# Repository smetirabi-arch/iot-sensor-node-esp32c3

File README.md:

# iot-sensor-node-esp32c3
Custom open-source ESP32-C3-02 IoT sensor node PCB featuring integrated TP4056 Li-ion battery charging with protection, BME280 environmental sensing, ambient light/sound sensors, I2C OLED display, and microSD/flash storage. Includes full KiCad hardware design, ESP32 firmware, and documentation. MIT licensed. Ideal for IoT prototyping.

SmartNode — ESP32-C3 IoT Sensor Node with Integrated Li-ion Power Management

Custom open-source ESP32-C3-02 IoT sensor node PCB featuring integrated TP4056 Li-ion battery charging with protection, BME280 environmental sensing, ambient light/sound sensors, I2C OLED display, and microSD/flash storage. Includes full KiCad hardware design, ESP32 firmware, and documentation. MIT licensed. Ideal for IoT prototyping.

Table of Contents

Overview
Key Features
System Architecture
Hardware Details

Microcontroller
Power Management
Sensors & Storage
Display & Indicators

Design Highlights
Applications
Repository Structure
Getting Started
Documentation
License

Overview

SmartNode is a custom-designed PCB for compact, battery-powered IoT applications, built around the ESP32-C3-02 SoC. The board integrates a complete power management subsystem using the TP4056 Li-ion battery charger IC, enabling safe, efficient charging of a single-cell Li-ion battery while supporting a rich set of onboard sensors and peripherals for real-world environmental monitoring and data logging.

This repository provides everything needed to build, program, and deploy the board: schematics, PCB layout files, firmware source code, and full documentation.

Key Features

Microcontroller: ESP32-C3-02 SoC — Wi-Fi and Bluetooth Low Energy (BLE) connectivity
Power Management: TP4056 IC for single-cell Li-ion charging with thermal regulation
Battery Protection: Under-voltage lockout (UVLO) and trickle charging
Environmental Sensing: BME280 (temperature, humidity, pressure), ambient light sensor, sound sensor
Storage: MicroSD card reader + onboard flash memory
Display: I2C OLED for real-time data visualization
Power Inputs: USB-C (charging + data) and JST LiPo connector
Status Indicators: LEDs for charging and full-charge states

System Architecture

SmartNode is organized into four functional subsystems, coordinated by the ESP32-C3-02 over I2C and SPI:

Processing & Connectivity — ESP32-C3-02 SoC
Power Management — TP4056 charging circuit and voltage regulation
Sensing & Storage — Environmental sensors, OLED display, SD card, flash memory
User Feedback — Status LEDs and display output

Hardware Details

Microcontroller

The ESP32-C3-02 is a RISC-V-based SoC with integrated Wi-Fi and BLE. It was chosen for its low power consumption, sufficient I2C/SPI/UART peripheral support, native wireless stack, and small footprint — making it well suited for compact, battery-powered IoT devices.

Power Management

TP4056 charging IC — provides constant-current/constant-voltage (CC/CV) charging, thermal regulation, and programmable charge current (set via external resistor)
Automatic charge termination — prevents overcharging once the battery reaches full voltage
UVLO & trickle charging — protects against deep discharge and safely recovers depleted batteries
USB-C — powers the system and charges the battery; also used for firmware flashing/debugging
JST LiPo connector — direct single-cell Li-ion/LiPo battery connection
Regulated power delivery — ensures stable operation whether powered via USB or battery

Sensors & Storage

ComponentFunctionBME280Temperature, humidity, and barometric pressure sensingAmbient light sensorEnvironmental light-level detectionSound sensorAmbient noise/acoustic sensingMicroSD card readerLocal, expandable data storageOnboard flash memoryFast, non-removable storage for firmware/cached data

All sensors communicate over I2C (SD storage typically over SPI), keeping the architecture modular and easily expandable with additional I2C devices.

Display & Indicators

I2C OLED display — real-time visualization of live sensor readings, no external device required
LED indicators — signal charging status (charging vs. fully charged)

Design Highlights

Integrated Power Supply — USB-C and TP4056 work together to manage charging and system power seamlessly
Modular, Expandable Architecture — additional I2C sensors can be added with minimal hardware changes
Safe, Efficient Charging — programmable current and automatic termination protect battery health
Compact, Reliable PCB Layout — optimized traces to minimize power loss, with thermal management around the TP4056 and other heat-sensitive components

Applications

IoT edge devices for environmental monitoring
Battery-powered data logging systems
General-purpose prototyping platform for ESP32-based hardware projects

Repository Structure

├── hardware/         # KiCad schematic and PCB layout files
├── firmware/          # ESP32-C3-02 source code
├── docs/
│   ├── datasheets/    # Component datasheets (TP4056, sensors, etc.)
│   ├── assembly.md    # Step-by-step assembly instructions
│   └── testing.md     # Testing and validation procedures
├── LICENSE
└── README.md

Documentation

Detailed documentation is available in the docs/ folder, including:

Component datasheets
Assembly instructions
Testing and validation procedures

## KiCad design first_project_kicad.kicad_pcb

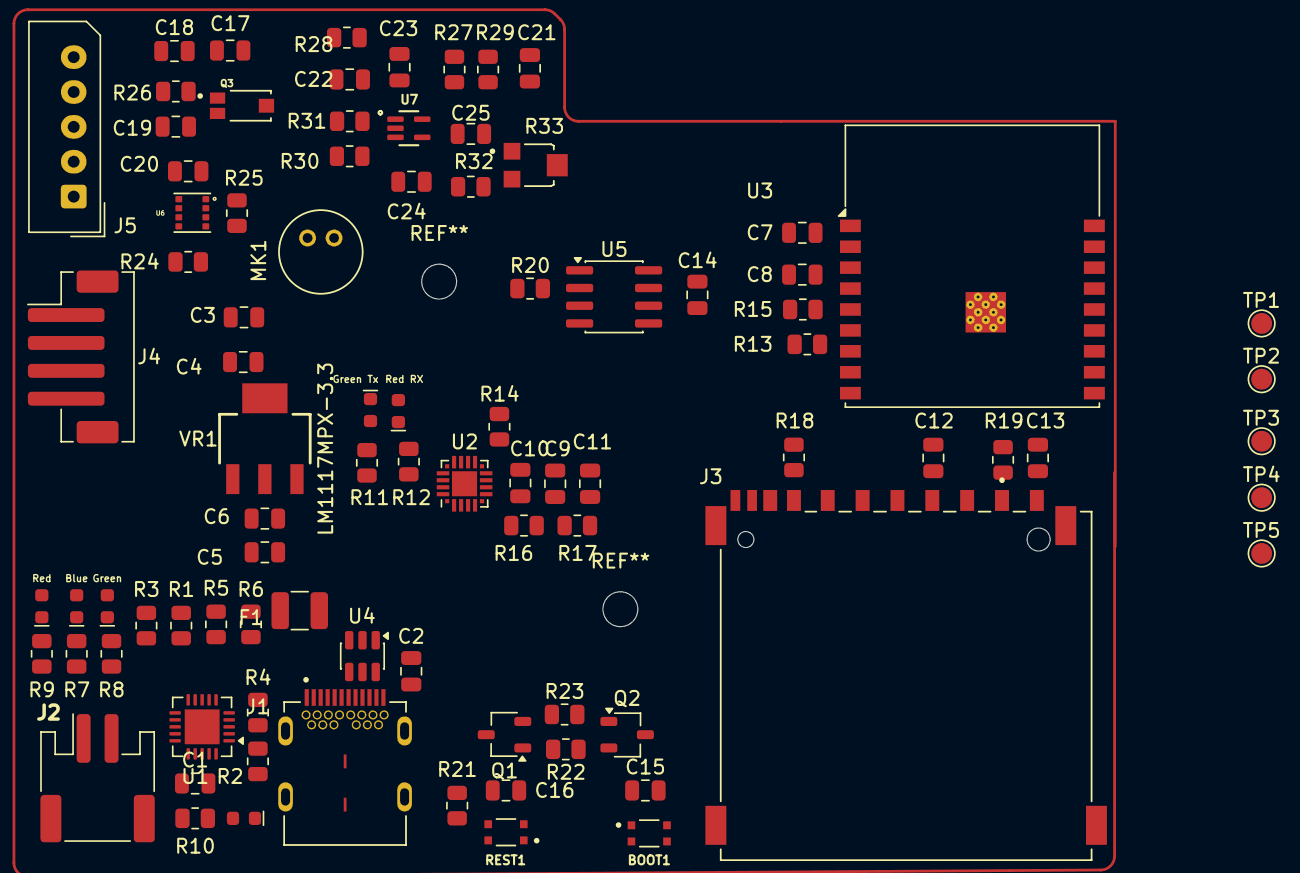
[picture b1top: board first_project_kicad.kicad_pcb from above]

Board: 4 copper layers, 89 parts (0 on the bottom side), 54 nets, no tracks yet.

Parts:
BOOT1: USLPT2819DT2TR; SW_USLPT2819DT2TR
C1, C11, C16: 1u; C_0805_2012Metric
C2, C7, C9, C13, C14, C15, C17, C20, C21, C23: 0.1u; C_0805_2012Metric
C3, C5, C6, C8, C12, C24: 10u; C_0805_2012Metric
C4: C; C_0805_2012Metric
C10: 4.7U; C_0805_2012Metric
C18, C19, C22: 10n; C_0805_2012Metric
C25: 100P; C_0805_2012Metric
D1: Blue; LED_0603_1608Metric
D2: Green; LED_0603_1608Metric
D3, D4: Red; LED_0603_1608Metric
D5: Green Tx; LED_0603_1608Metric
D6: Red RX; LED_0603_1608Metric
F1: 0ZCH0110AF2E; Fuse_1210_3225Metric
J1: SS-52400-002; BELFUSE_SS-52400-002
J2: B2B-PH-SM4-TB; JST_PH_S2B-PH-SM4-TB_1x02-1MP_P2.00mm_Horizontal
J3: GSD090012SEU; AMPHENOL_GSD090012SEU
J4: B4B-XH-AM_(LF)(SN); JST_PH_B4B-PH-SM4-TB_1x04-1MP_P2.00mm_Vertical
J5: 535170530; Molex_SPOX_5267-05A_1x05_P2.50mm_Vertical
MK1: CMC-5042PF-AC; CUI_CMC-5042PF-AC
Q1, Q2: BC817-40; TSOT-23
Q3: TEMT6000X01; TRANS_TEMT6000X01
R1: 2k; R_0805_2012Metric
R2, R4: 5k; R_0805_2012Metric
R3: 20k; R_0805_2012Metric
R5, R6, R13, R15, R18, R19, R20, R21, R22, R23, R26: 10k; R_0805_2012Metric
R7, R8, R9: 470; R_0805_2012Metric
R10, R11, R12: 330; R_0805_2012Metric
R14, R30: 1K; R_0805_2012Metric
R16: 47K5; R_0805_2012Metric
R17: 22K1; R_0805_2012Metric
R24, R25: 4K7; R_0805_2012Metric
R27, R29: 2K; R_0805_2012Metric
R28, R31: 1M; R_0805_2012Metric
R32: 22K; R_0805_2012Metric
R33: 35WR100KLFTR; TRIM_35WR100KLFTR
REST1: USLPT2819DT2TR; SW_USLPT2819DT2TR
TP1: Test MOSI; TestPoint_Pad_D1.5mm
TP2: Test MISO; TestPoint_Pad_D1.5mm
TP3: Test SCLK; TestPoint_Pad_D1.5mm
TP4: Test SD; TestPoint_Pad_D1.5mm
TP5: Test CS; TestPoint_Pad_D1.5mm
U1: MCP73871; QFN-20-1EP_4x4mm_P0.5mm_EP2.5x2.5mm
U2: CP2102N-A02-GQFN20; SiliconLabs_QFN-20-1EP_3x3mm_P0.5mm_EP1.8x1.8mm
U3: ESP32-C3-WROOM-02-H4; ESP32-C3-WROOM-02
U4: USBLC6-2SC6; TSOT-23-6
U5: W25Q32JVSSIQ; SOIC-8_3.9x4.9mm_P1.27mm
U6: BME280; PSON65P250X250X100-8N
U7: MAX4466EXK; SOT65P210X110-5N
VR1: LM1117MPX-3.3; VREG_LM1117MPX-3.3

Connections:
+3.3V: C3.1, C4.1, C7.1, C8.1, C9.1, C10.1, C12.1, C13.1, C14.1, C17.1, C20.1, C23.1, J3.4 (VDD1), J4.1, J5.1, Q3.3, R14.1, R19.2, R21.2, R24.1, R25.1, R27.2, R28.2, U2.6 (VDD), U2.7 (VREGIN), U3.1 (3V3), U5.3 (~WP(IO2)), U5.7 (~HOLD/~RESET(IO3)), U5.8 (VCC), U6.2 (CSB), U6.6 (VDDIO), U6.8 (VDD), U7.5 (VCC), VR1.2 (VOUT_2), VR1.4 (VOUT_4)
+5C: C5.1, C6.1, VR1.3 (VIN)
/+5V: C1.2, U1.1 (OUT), U1.2 (VPCC), U1.18 (IN), U1.19 (IN), U1.20 (OUT)
/+5V_USB: F1.1, U1.4 (PROG2), U1.17 (CE)
/ESP32_C3_02/BOOT: BOOT1.1, BOOT1.2, C15.1, Q2.3, U3.8 (IO9)
/ESP32_C3_02/CS: TP5.1, U3.10 (IO10), U5.1 (~CS)
/ESP32_C3_02/CS_SD: J3.1 (CD/DAT3), R19.1, TP4.1, U3.4 (IO5)
/ESP32_C3_02/DTR: Q2.2, R22.1, U2.15 (CTS)
/ESP32_C3_02/EN: C16.1, Q1.3, R21.1, REST1.3, REST1.4, U3.2 (EN)
/ESP32_C3_02/GPIO08: J5.2, U3.7 (IO8)
/ESP32_C3_02/GPIO18: J5.3, U3.13 (IO18)
/ESP32_C3_02/GPIO19: J5.4, U3.14 (IO19)
/ESP32_C3_02/MIC_OUT: C25.1, R33.1, R33.2, U3.18 (IO0), U7.4 (OUT)
/ESP32_C3_02/MISO_DO: R18.2, R20.1, TP2.1, U3.16 (IO2)
/ESP32_C3_02/MOSI_DI: J3.2 (CMD), R13.2, TP1.1, U5.5 (DI(IO0))
/ESP32_C3_02/PHOTO_C: C18.1, C19.1, Q3.1, R26.2, U3.17 (IO1)
/ESP32_C3_02/RTS: Q1.2, R23.1, U2.16 (RTS)
/ESP32_C3_02/RX_TX: U2.17 (RXD), U3.12 (TXD)
/ESP32_C3_02/SCL: J4.3, R24.2, U3.15 (IO3), U6.4 (SCK)
/ESP32_C3_02/SCLK: J3.5 (CLK), R15.1, TP3.1, U5.6 (CLK)
/ESP32_C3_02/SDA: J4.2, R25.2, U3.3 (IO4), U6.3 (SDI)
/ESP32_C3_02/TX_RX: U2.18 (TXD), U3.11 (RXD)
/ESP32_C3_02/USB_D+: U2.4 (D+), U4.3
/USB_DN: J1.A7 (DN1), J1.B7 (DN2), U4.6
/USB_DP: J1.A6 (DP1), J1.B6 (DP2), U4.4
/VBAT: J2.2, U1.14 (V_{BAT}), U1.15 (V_{BAT}), U1.16 (V_{BAT_SENSE})
/VBUS: C2.1, F1.2, J1.A4 (VBUSA1), J1.A9 (VBUSA2), J1.B4 (VBUSB1), J1.B9 (VBUSB2), R17.2, U4.5
GND: BOOT1.3, BOOT1.4, C1.1, C2.2, C3.2, C4.2, C5.2, C6.2, C7.2, C8.2, C9.2, C10.2, C11.2, C12.2, C13.2, C14.2, C15.2, C16.2, C17.2, C18.2, C19.2, C20.2, C21.1, C23.2, C24.2, J1.A1 (GNDA1), J1.A12 (GNDA2), J1.B1 (GNDB1), J1.B12 (GNDB2), J1.G1 (GND/SHIELD), J1.G2 (GND/SHIELD), J1.G3 (GND/SHIELD), J1.G4 (GND/SHIELD), J1.S1 (GND/SHIELD), J1.S2 (GND/SHIELD), J1.S3 (GND/SHIELD), J1.S4 (GND/SHIELD), J2.1, J3.3 (VSS1), J3.6 (VSS2), J3.8 (DAT1), J3.9 (DAT2), J3.G1 (SHIELD_GND), J3.G2 (SHIELD_GND), J3.G3 (SHIELD_GND), J3.G4 (SHIELD_GND), J4.4, J5.5, MK1.GND, R1.1, R2.1, R3.1, R4.1, R5.1, R6.1, R10.1, R16.1, R26.1, R31.1, REST1.1, REST1.2, U1.3 (SEL), U1.10 (V_{SS}), U1.11 (V_{SS}), U1.21 (V_{SS}), U2.3 (GND), U2.12 (GND), U3.9 (GND), U3.19 (GND), U4.2, U5.4 (GND), U6.1 (GND), U6.5 (SDO), U6.7 (GND), U7.2 (GND), VR1.1 (GND)
unnamed: C21.2, R27.1, R29.2
unnamed: C22.2, MK1.OUT, R29.1
unnamed: C24.1, R30.1
unnamed: J1.A5 (CC1), R2.2
unnamed: J1.B5 (CC2), R4.2
unnamed: J3.7 (DAT0), R18.1
unnamed: Q1.1, R22.2
unnamed: Q2.1, R23.2
unnamed: R32.1, R33.3
unnamed: R1.2, U1.13 (PROG1)
unnamed: R3.2, U1.12 (PROG3)
unnamed: R8.2, U1.8 (STAT1/~LBO)
unnamed: R7.2, U1.7 (STAT2)
unnamed: R5.2, U1.5 (THERM)
unnamed: R9.2, U1.6 (~PG)
unnamed: R6.2, U1.9 (~TE)
unnamed: U2.5 (D-), U4.1
unnamed: R11.1, U2.20 (GPIO2/TXT)
unnamed: R12.1, U2.19 (GPIO3/RXT)
unnamed: R14.2, U2.9 (RSTB)
unnamed: C11.1, R16.2, R17.1, U2.8 (VBUS)
unnamed: R15.2, U3.5 (IO6)
unnamed: R13.1, U3.6 (IO7)
unnamed: R20.2, U5.2 (DO(IO1))
unnamed: C22.1, R28.1, R31.2, U7.1 (IN+)
unnamed: C25.2, R30.2, R32.2, U7.3 (IN-)
